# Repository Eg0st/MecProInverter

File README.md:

# Goal
This project is a student project at the Munich University of Applied Sciences.
The aim is to build and operate an inverter with an output of 3.6 kW,
which is supplied with 230 volts and can operate a motor in the frequency range of 10 to 500 Hz.
The ESP32-S3 and the SimpleFoc Bilbiotek were used for this.

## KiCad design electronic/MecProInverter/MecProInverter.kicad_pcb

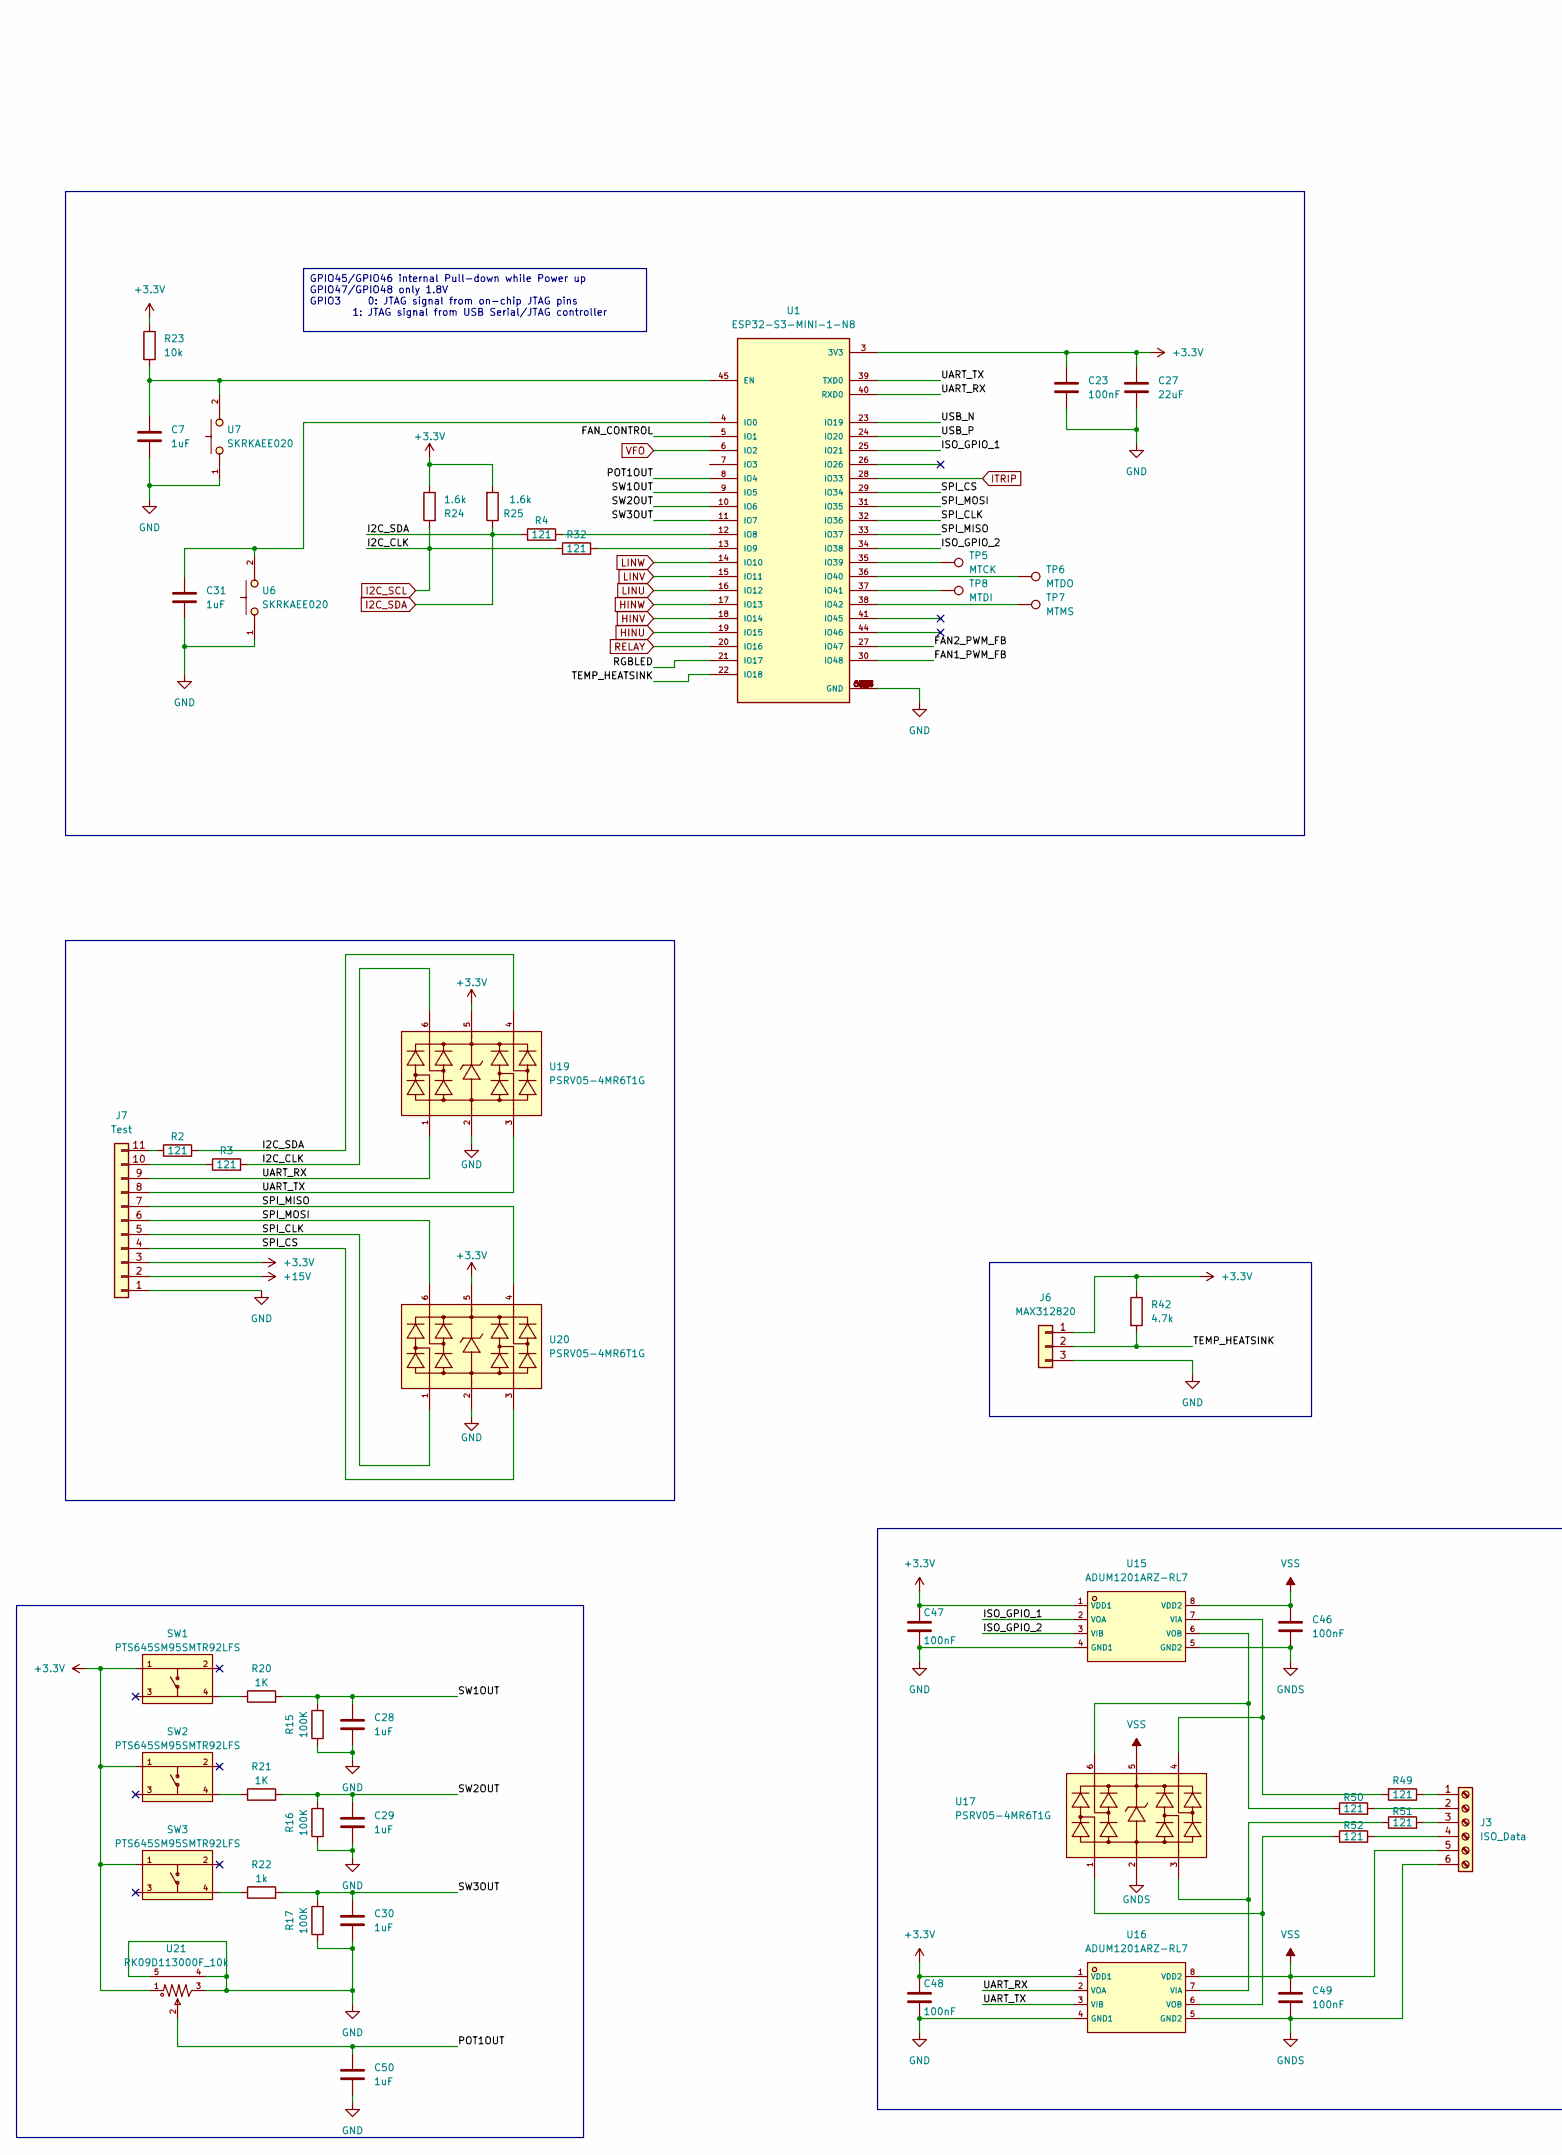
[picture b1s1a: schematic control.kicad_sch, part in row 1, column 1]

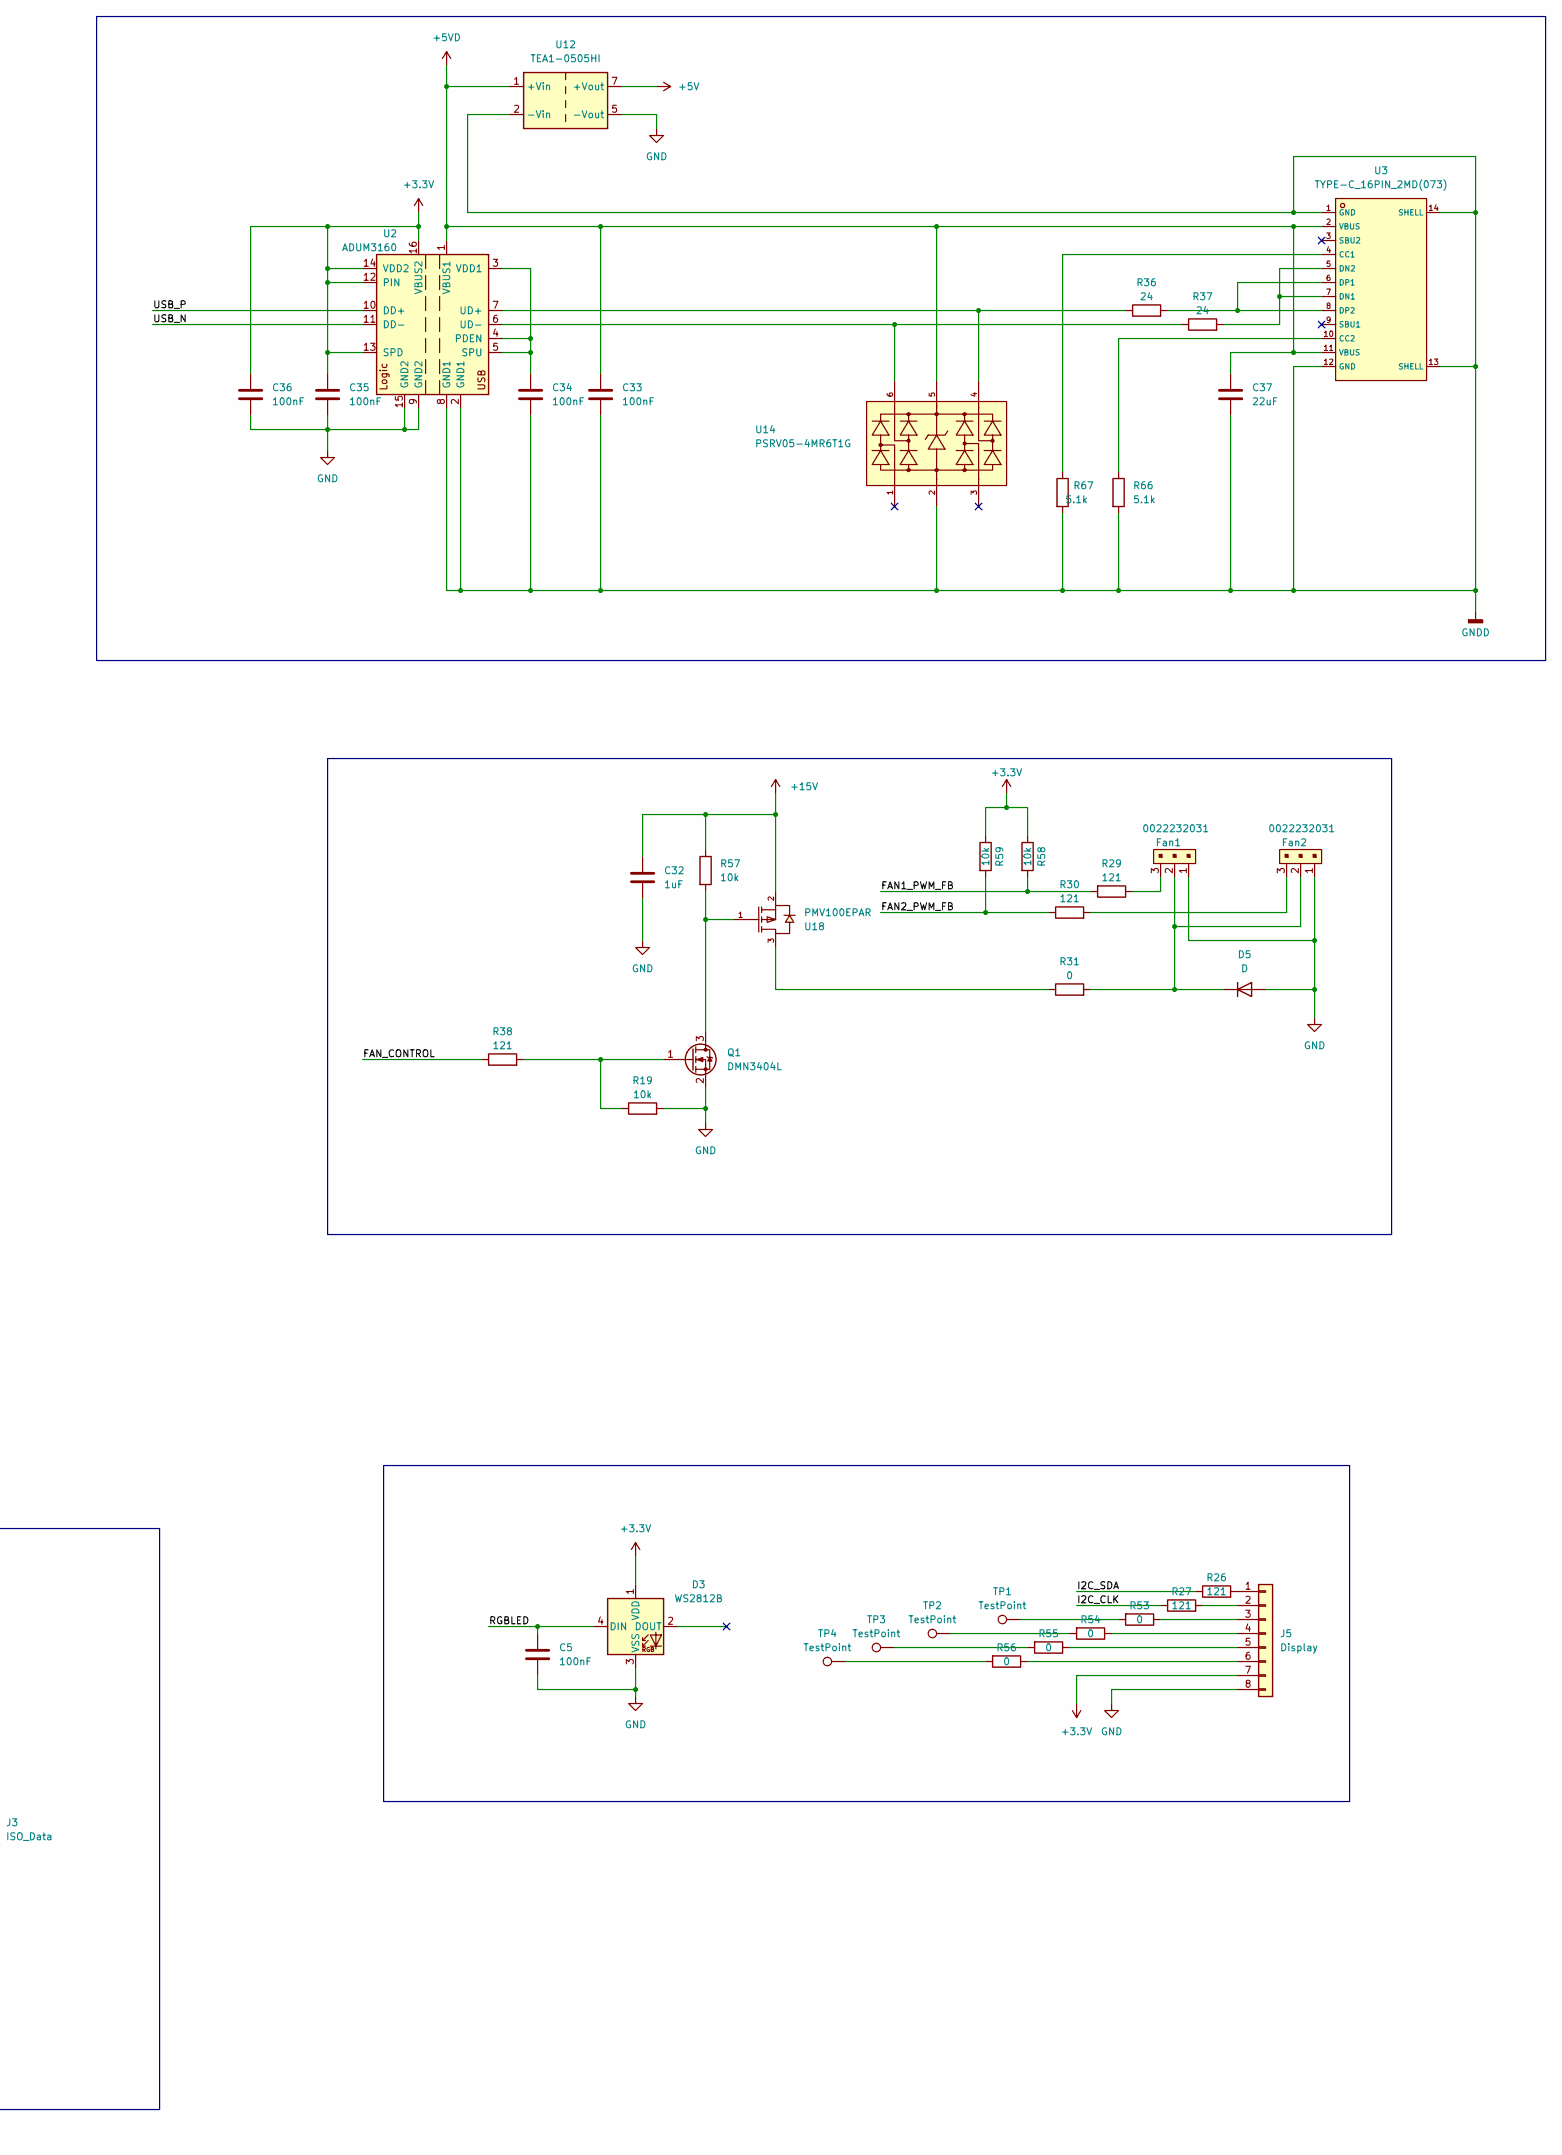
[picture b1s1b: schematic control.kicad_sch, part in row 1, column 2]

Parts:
C5, C23, C33, C34, C35, C36, C46, C47, C48, C49: 100nF; C_0603_1608Metric
C7, C28, C29, C30, C31, C32, C50: 1uF; C_0603_1608Metric
C27, C37: 22uF; C_0603_1608Metric
D3: WS2812B; LED_WS2812B_PLCC4_5.0x5.0mm_P3.2mm
D5: D; D_SOD-123
Fan1, Fan2: 0022232031; CONN-TH_3P-P2.54_22-23-2031; MPN 0022232031; Digi-Key_PN WM4201-ND
J3: ISO_Data; TerminalBlock_Phoenix_MPT-0,5-6-2.54_1x06_P2.54mm_Horizontal
J5: Display; Adafruit_938
J6: MAX312820; PinHeader_1x03_P2.54mm_Vertical
J7: Test; PinHeader_1x11_P2.54mm_Vertical
Q1: DMN3404L; SOT-23
R2, R3, R4, R26, R27, R29, R30, R32, R38, R49, R50, R51, R52: 121; R_0603_1608Metric
R15, R16, R17: 100K; R_0603_1608Metric
R19, R23, R57, R58, R59: 10k; R_0603_1608Metric
R20, R21: 1K; R_0603_1608Metric
R22: 1k; R_0603_1608Metric
R24, R25: 1.6k; R_0603_1608Metric
R31: 0; R_1206_3216Metric
R36, R37: 24; R_0603_1608Metric
R42: 4.7k; R_0603_1608Metric
R53, R54, R55, R56: 0; R_0603_1608Metric
R66, R67: 5.1k; R_0603_1608Metric
SW1, SW2, SW3: PTS645SM95SMTR92LFS; KEY-SMD_4P-L6.1-W6.1-P4.50-LS9.0; LCSC C221884
TP1, TP2, TP3, TP4: TestPoint; TestPoint_Pad_D1.5mm
TP5: MTCK; TestPoint_Pad_D1.5mm
TP6: MTDO; TestPoint_Pad_D1.5mm
TP7: MTMS; TestPoint_Pad_D1.5mm
TP8: MTDI; TestPoint_Pad_D1.5mm
U1: ESP32-S3-MINI-1-N8; BULETM-SMD_ESP32-S3-MINI-1-N8; PARTREV v0.6
U2: ADUM3160; SOIC-16W_7.5x10.3mm_P1.27mm
U3: TYPE-C_16PIN_2MD(073); USB-C-SMD_TYPE-C-6PIN-2MD-073; LCSC C2765186
U6, U7: SKRKAEE020; SW-SMD_L3.9-W3.0-P4.45; LCSC C115357
U12: TEA1-0505HI; Converter_DCDC_TRACO_TEA1HI-xxxx_THT
U14, U17, U19, U20: PSRV05-4MR6T1G; SOT-23-6_L2.9-W1.6-P0.95-LS2.8-BL; LCSC C2936987
U15, U16: ADUM1201ARZ-RL7; SOIC-8_L4.9-W3.9-P1.27-LS6.0-BL; LCSC C9669
U18: PMV100EPAR; SOT-23-3_L2.9-W1.3-P1.90-LS2.3-BR; LCSC C3290636
U21: RK09D113000F_10k; RES-ADJ-TH_RK09D1130C4G; LCSC C470317

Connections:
+3.3V: C23.1, C27.1, C35.1, C36.1, C47.1, C48.1, D3.1 (VDD), J5.7, J6.1, J7.3, R23.1, R24.1, R25.2, R42.1, R58.1, R59.1, SW1.1, SW2.1, SW3.1, U1.3 (3V3), U2.12 (PIN), U2.13 (SPD), U2.14 (VDD2), U2.16 (VBUS2), U15.1 (VDD1), U16.1 (VDD1), U19.5, U20.5, U21.1; also elsewhere on the board
+5V: U12.7 (+Vout); also elsewhere on the board
+5VD: C33.1, C37.1, U2.1 (VBUS1), U3.2 (VBUS), U3.11 (VBUS), U12.1 (+Vin), U14.5
+15V: C32.1, J7.2, R57.1, U18.2 (S); also elsewhere on the board
/Control/FAN1_PWM_FB: R29.2, R58.2, U1.30 (IO48)
/Control/FAN2_PWM_FB: R30.1, R59.2, U1.27 (IO47)
/Control/FAN_CONTROL: R38.1, U1.5 (IO1)
/Control/ISO_GPIO_1: U1.25 (IO21), U15.2 (VOA)
/Control/ISO_GPIO_2: U1.34 (IO38), U15.3 (VIB)
/Control/POT1OUT: C50.1, U1.8 (IO4), U21.2
/Control/RGBLED: C5.1, D3.4 (DIN), U1.21 (IO17)
/Control/SPI_CLK: J7.5, U1.32 (IO36), U20.1
/Control/SPI_CS: J7.4, U1.29 (IO34), U20.3
/Control/SPI_MISO: J7.7, U1.33 (IO37), U20.4
/Control/SPI_MOSI: J7.6, U1.31 (IO35), U20.6
/Control/SW1OUT: C28.1, R15.2, R20.2, U1.9 (IO5)
/Control/SW2OUT: C29.1, R16.2, R21.2, U1.10 (IO6)
/Control/SW3OUT: C30.1, R17.2, R22.2, U1.11 (IO7)
/Control/TEMP_HEATSINK: J6.2, R42.2, U1.22 (IO18)
/Control/UART_RX: J7.9, U1.40 (RXD0), U16.2 (VOA), U19.1
/Control/UART_TX: J7.8, U1.39 (TXD0), U16.3 (VIB), U19.3
/Control/USB_N: U1.23 (IO19), U2.11 (DD-)
/Control/USB_P: U1.24 (IO20), U2.10 (DD+)
GND: C5.2, C7.2, C23.2, C27.2, C28.2, C29.2, C30.2, C31.2, C32.2, C35.2, C36.2, C47.2, C48.2, C50.2, D3.3 (VSS), D5.2 (A), Fan1.1, Fan2.1, J5.8, J6.3, J7.1, Q1.2 (S), R15.1, R16.1, R17.1, R19.2, U1.1 (GND), U1.2 (GND), U1.42 (GND), U1.43 (GND), U1.46 (GND), U1.47 (GND), U1.48 (GND), U1.49 (GND), U1.50 (GND), U1.51 (GND), U1.52 (GND), U1.53 (GND), U1.54 (GND), U1.55 (GND), U1.56 (GND), U1.57 (GND), U1.58 (GND), U1.59 (GND), U1.60 (GND), U1.61 (GND), U1.61_1 (GND), U1.61_2 (GND), U1.61_3 (GND), U1.61_4 (GND), U1.61_5 (GND), U1.61_6 (GND), U1.61_7 (GND), U1.61_8 (GND), U1.62 (GND), U1.63 (GND), U1.64 (GND), U1.65 (GND), U2.9 (GND2), U2.15 (GND2), U6.1, U7.1, U12.5 (-Vout), U15.4 (GND1), U16.4 (GND1), U19.2, U20.2, U21.3, U21.4, U21.5; also elsewhere on the board
GNDD: C33.2, C34.2, C37.2, R66.2, R67.2, U2.2 (GND1), U2.8 (GND1), U3.1 (GND), U3.12 (GND), U3.13 (SHELL), U3.14 (SHELL), U12.2 (-Vin), U14.2
GNDS: C46.2, C49.2, J3.6, U15.5 (GND2), U16.5 (GND2), U17.2
HINU: U1.19 (IO15); also elsewhere on the board
HINV: U1.18 (IO14); also elsewhere on the board
HINW: U1.17 (IO13); also elsewhere on the board
I2C_SCL: R3.2, R24.2, R27.1, R32.1, U19.6; also elsewhere on the board
I2C_SDA: R2.2, R4.1, R25.1, R26.1, U19.4; also elsewhere on the board
ITRIP: U1.28 (IO33); also elsewhere on the board
LINU: U1.16 (IO12); also elsewhere on the board
LINV: U1.15 (IO11); also elsewhere on the board
LINW: U1.14 (IO10); also elsewhere on the board
unnamed: D5.1 (K), Fan1.2, Fan2.2, R31.2
unnamed: Fan1.3, R29.1
unnamed: Fan2.3, R30.2
unnamed: J3.1, R49.1
unnamed: J3.2, R50.2
unnamed: J3.3, R51.2
unnamed: J3.4, R52.2
unnamed: J5.1, R26.2
unnamed: J5.2, R27.2
unnamed: J5.3, R53.1
unnamed: J5.4, R54.1
unnamed: J5.5, R55.1
unnamed: J5.6, R56.1
unnamed: J7.10, R3.1
unnamed: J7.11, R2.1
unnamed: R20.1, SW1.4
unnamed: R21.1, SW2.4
unnamed: R22.1, SW3.4
unnamed: R53.2, TP1.1
unnamed: R54.2, TP2.1
unnamed: R55.2, TP3.1
unnamed: R56.2, TP4.1
unnamed: C7.1, R23.2, U1.45 (EN), U7.2
unnamed: C31.1, U1.4 (IO0), U6.2
unnamed: R4.2, U1.12 (IO8)
unnamed: R32.2, U1.13 (IO9)
unnamed: TP5.1, U1.35 (IO39)
unnamed: TP6.1, U1.36 (IO40)
unnamed: TP8.1, U1.37 (IO41)
unnamed: TP7.1, U1.38 (IO42)
unnamed: C34.1, U2.3 (VDD1), U2.4 (PDEN), U2.5 (SPU)
unnamed: R36.1, U2.7 (UD+), U14.4
unnamed: R37.1, U2.6 (UD-), U14.6
unnamed: R67.1, U3.4 (CC1)
unnamed: R66.1, U3.10 (CC2)
unnamed: R37.2, U3.5 (DN2), U3.7 (DN1)
unnamed: R36.2, U3.6 (DP1), U3.8 (DP2)
unnamed: R49.2, U15.7 (VIA), U17.4
unnamed: R50.1, U15.6 (VOB), U17.6
unnamed: R51.1, U16.7 (VIA), U17.3
unnamed: R52.1, U16.6 (VOB), U17.1
unnamed: R31.1, U18.3 (D)
RELAY: U1.20 (IO16); also elsewhere on the board
VFO: U1.6 (IO2); also elsewhere on the board
VSS: C46.1, C49.1, J3.5, U15.8 (VDD2), U16.8 (VDD2), U17.5

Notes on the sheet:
GPIO45/GPIO46 internal Pull-down while Power up GPIO47/GPIO48 only 1.8V GPIO3 0: JTAG signal from on-chip JTAG pins 1: JTAG signal from USB Serial/JTAG controller

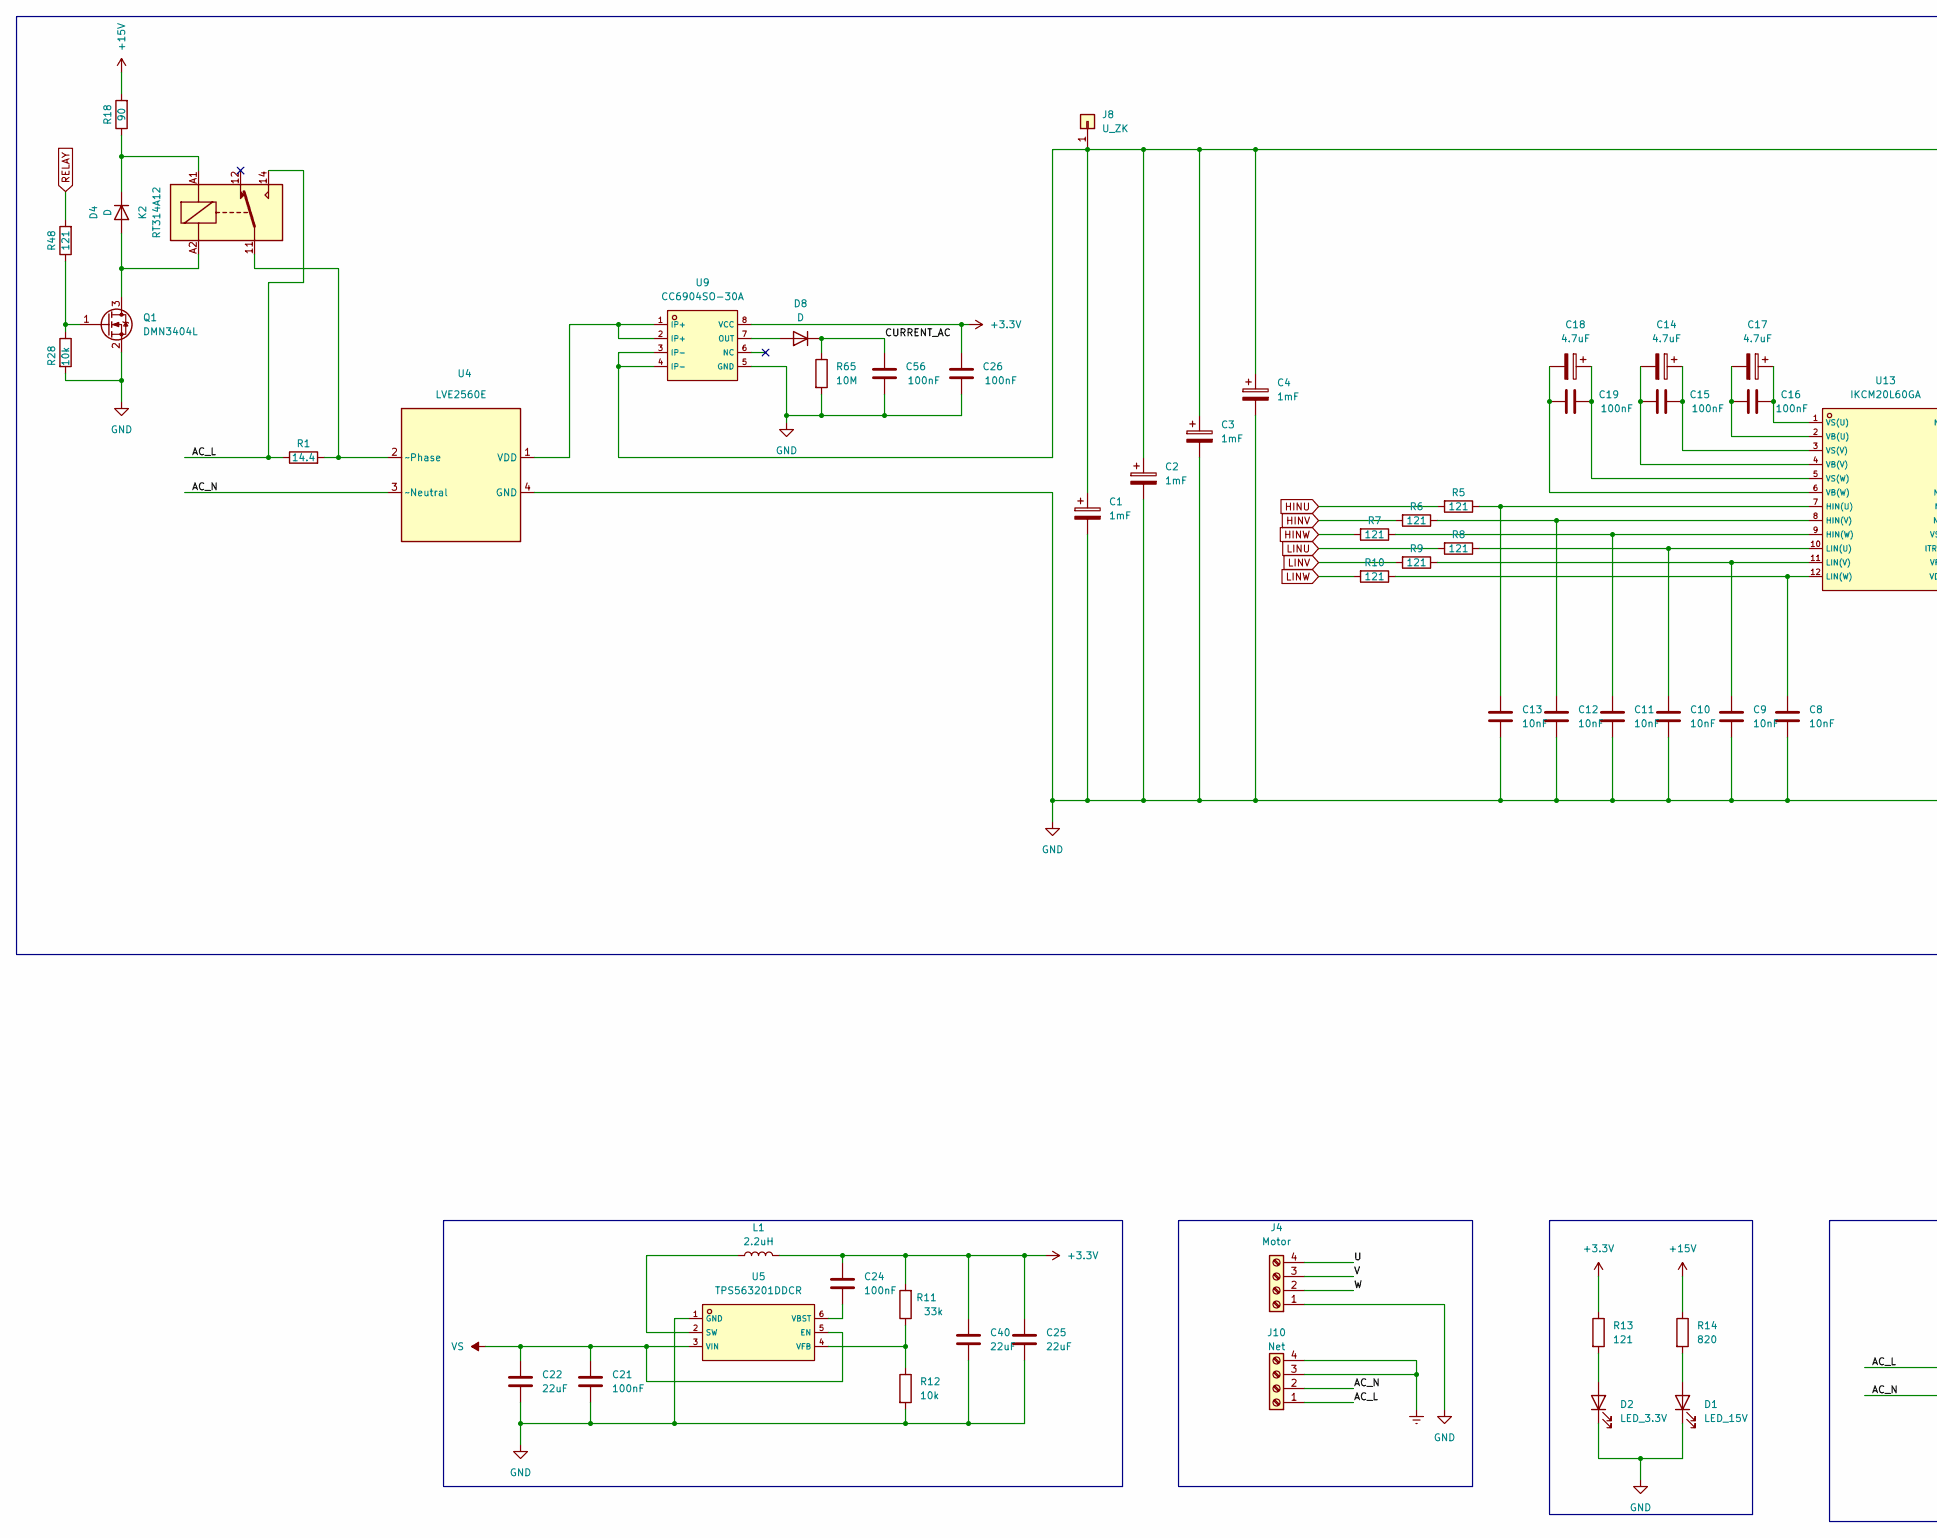
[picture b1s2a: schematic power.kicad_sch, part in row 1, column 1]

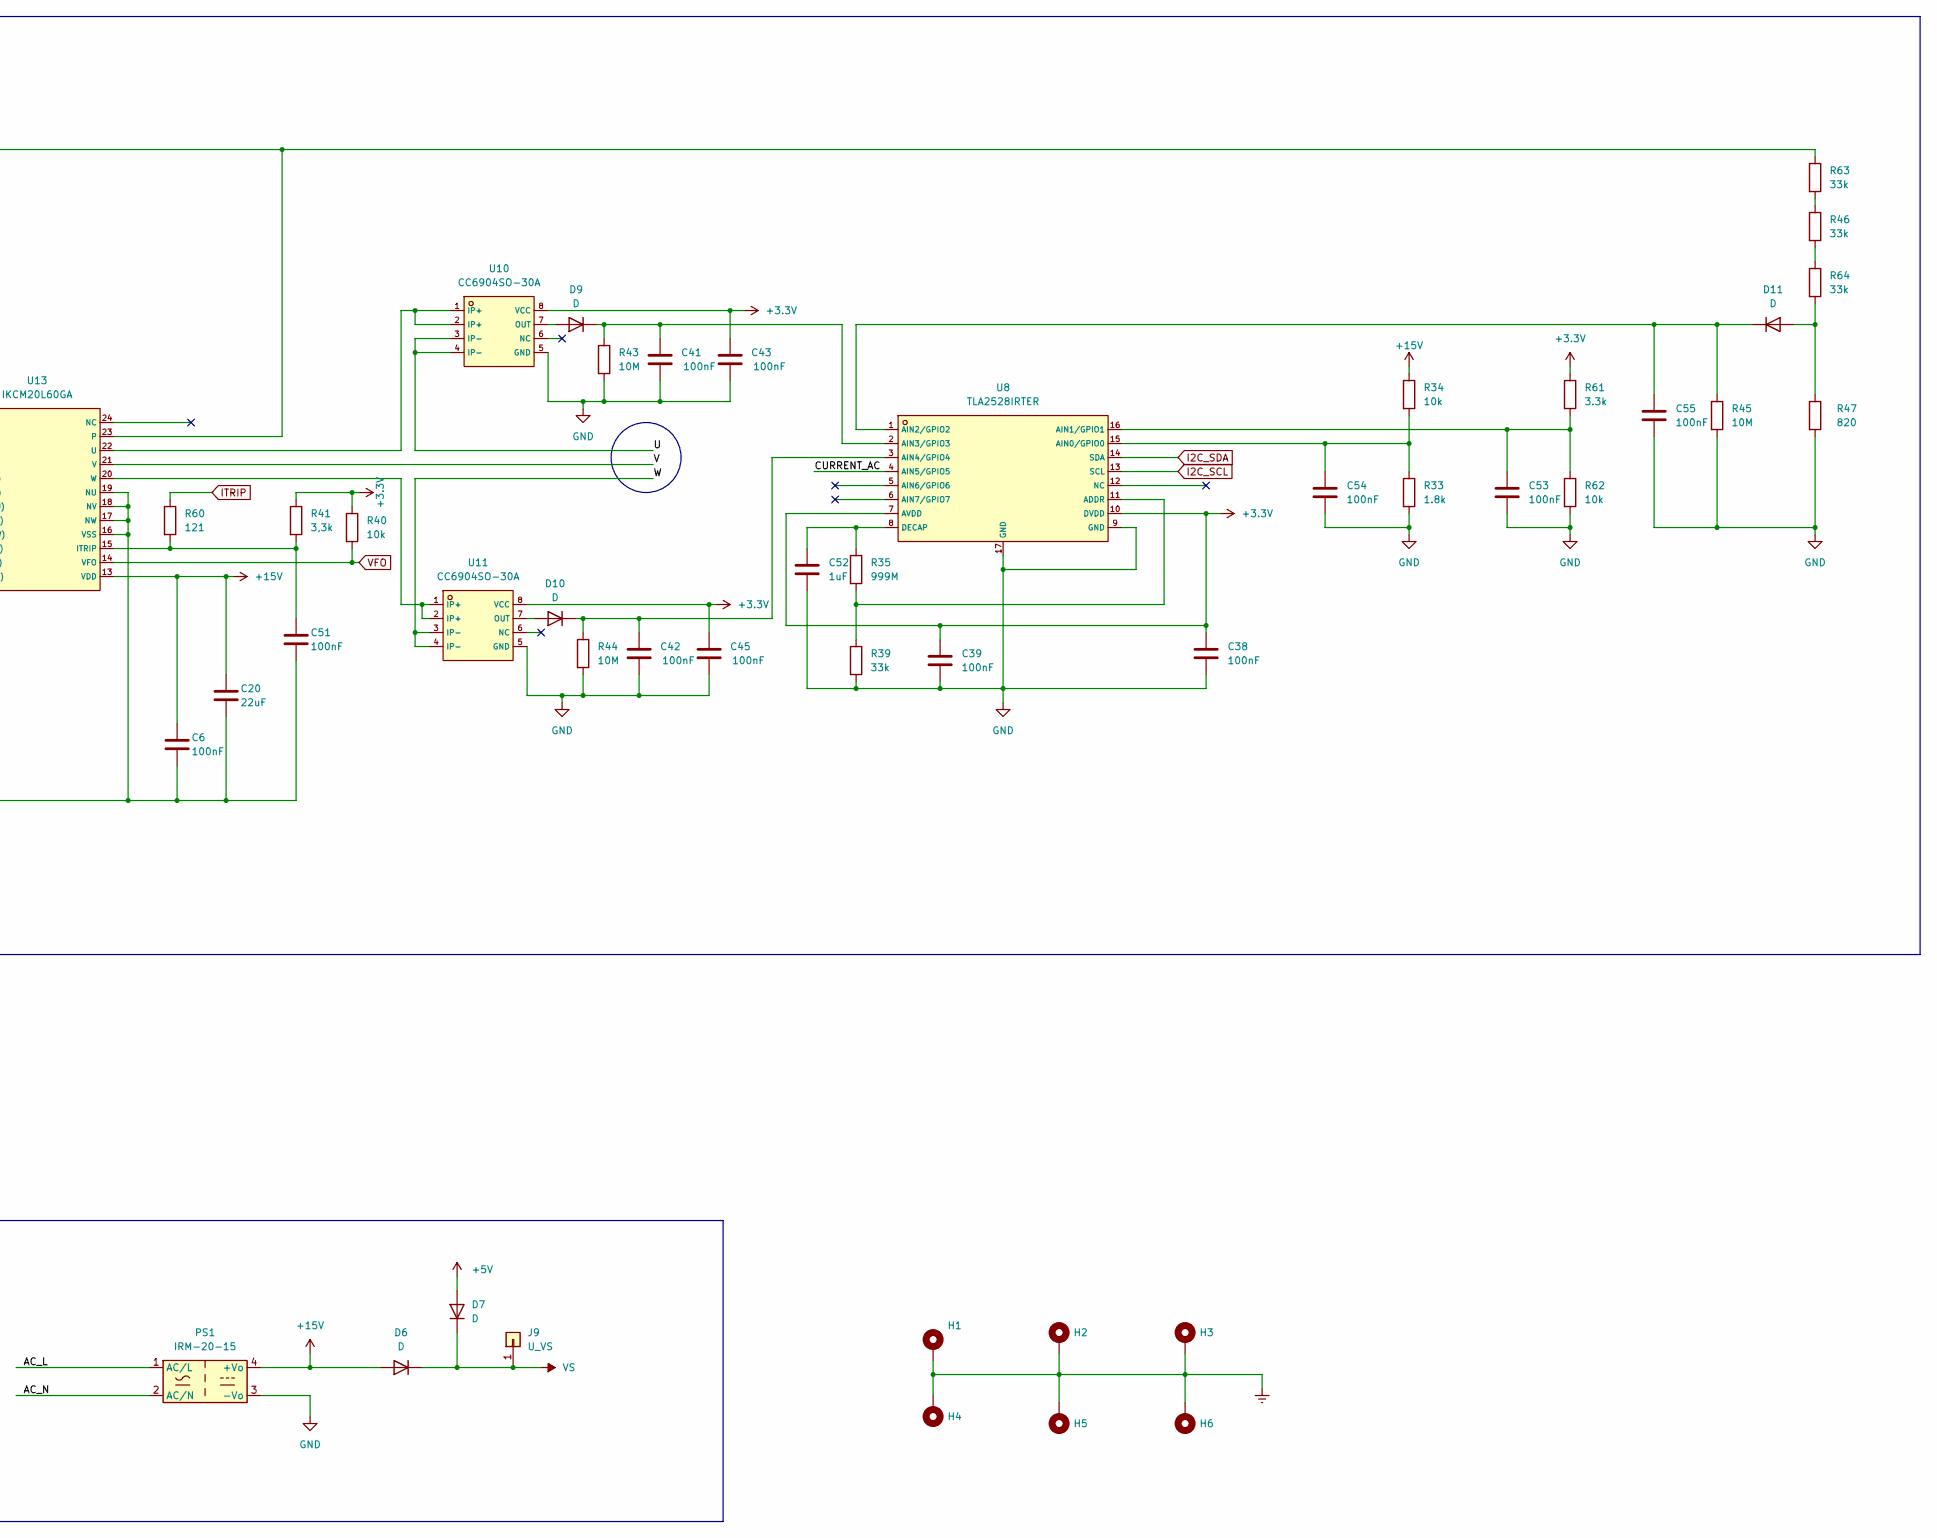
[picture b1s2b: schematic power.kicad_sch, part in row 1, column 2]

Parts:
C1, C2, C3, C4: 1mF; ESMQ351VSN102MA50S
C6, C15, C16, C19, C21, C24, C26, C38, C39, C41, C42, C43, C45, C51, C53, C54, C55, C56: 100nF; C_0603_1608Metric
C8, C9, C10, C11, C12, C13: 10nF; C_0603_1608Metric
C14, C17, C18: 4.7uF; C_0603_1608Metric
C20, C22, C25, C40: 22uF; C_0603_1608Metric
C52: 1uF; C_0603_1608Metric
D1: LED_15V; LED_0603_1608Metric
D2: LED_3.3V; LED_0603_1608Metric
D4, D6, D7: D; D_SOD-123
D8, D9, D10, D11: D; D_0603_1608Metric
H1, H2, H3, H4, H5, H6: MountingHole_3.2mm_M3_DIN965_Pad_TopBottom
J4: Motor; TerminalBlock_Phoenix_PT-1,5-4-5.0-H_1x04_P5.00mm_Horizontal
J8: U_ZK; PinHeader_1x01_P2.54mm_Vertical
J9: U_VS; PinHeader_1x01_P2.54mm_Vertical
J10: Net; TerminalBlock_Phoenix_PT-1,5-4-5.0-H_1x04_P5.00mm_Horizontal
K2: RT314A12; Relay_SPDT_Schrack-RT1-16A-FormC_RM5mm
L1: 2.2uH; L_Bourns_SRP7028A_7.3x6.6mm
PS1: IRM-20-15; Converter_ACDC_MeanWell_IRM-20-xx_THT
Q1: DMN3404L; SOT-23
R1: 14.4; PWR220T-20
R5, R6, R7, R8, R9, R10, R13, R48, R60: 121; R_0603_1608Metric
R11, R39: 33k; R_0603_1608Metric
R12, R28, R34, R40, R62: 10k; R_0603_1608Metric
R14, R47: 820; R_0603_1608Metric
R18: 90; R_1206_3216Metric
R33: 1.8k; R_0603_1608Metric
R35: 999M; R_0603_1608Metric
R41: 3,3k; R_0603_1608Metric
R43, R44, R45, R65: 10M; R_0603_1608Metric
R46, R63, R64: 33k; R_1206_3216Metric
R61: 3.3k; R_0603_1608Metric
U4: LVE2560E
U5: TPS563201DDCR; SOT-23-6_L2.9-W1.6-P0.95-LS2.8-BL; LCSC C116592
U8: TLA2528IRTER; WQFN-16_L3.0-W3.0-P0.50-TL-EP1.7; LCSC C2866175
U9, U10, U11: CC6904SO-30A; SOP-8_L4.9-W3.9-P1.27-LS6.0-BL; LCSC C521203
U13: IKCM20L60GA; DIP-24_L36.0-W21.0-P1.60-LS28.6-TL; LCSC C536161

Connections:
+3.3V: C24.1, C25.1, C26.2, C38.2, C39.1, C40.1, C43.2, C45.2, L1.2, R11.2, R13.1, R40.1, R41.1, R61.1, U8.7 (AVDD), U8.10 (DVDD), U9.8 (VCC), U10.8 (VCC), U11.8 (VCC); also elsewhere on the board
+5V: D7.2 (A); also elsewhere on the board
+15V: C6.1, C20.1, D6.2 (A), PS1.4 (+Vo), R14.1, R18.2, R34.1, U13.13 (VDD); also elsewhere on the board
/Power/AC_L: J10.1, K2.14, PS1.1 (AC/L), R1.1
/Power/AC_N: J10.2, PS1.2 (AC/N), U4.3 (~Neutral)
/Power/CURRENT_AC: C56.2, D8.1 (K), R65.1, U8.4 (AIN5/GPIO5)
/Power/U: J4.4, U10.3 (IP-), U10.4 (IP-)
/Power/V: J4.3, U13.21 (V)
/Power/W: J4.2, U11.3 (IP-), U11.4 (IP-)
Earth: H1.1, H2.1, H3.1, H4.1, H5.1, H6.1, J10.3, J10.4
GND: C1.2, C2.2, C3.2, C4.2, C6.2, C8.2, C9.2, C10.2, C11.2, C12.2, C13.2, C20.2, C21.2, C22.2, C25.2, C26.1, C38.1, C39.2, C40.2, C41.1, C42.1, C43.1, C45.1, C51.2, C52.2, C53.2, C54.2, C55.2, C56.1, J4.1, PS1.3 (-Vo), Q1.2 (S), R12.2, R28.2, R33.2, R39.2, R43.2, R44.2, R45.2, R47.2, R62.2, R65.2, U4.4 (GND), U5.1 (GND), U8.9 (GND), U8.17 (GND), U9.5 (GND), U10.5 (GND), U11.5 (GND), U13.16 (VSS), U13.17 (NW), U13.18 (NV), U13.19 (NU); also elsewhere on the board
HINU: R5.2; also elsewhere on the board
HINV: R6.2; also elsewhere on the board
HINW: R7.2; also elsewhere on the board
I2C_SCL: U8.13 (SCL); also elsewhere on the board
I2C_SDA: U8.14 (SDA); also elsewhere on the board
ITRIP: R60.1; also elsewhere on the board
LINU: R8.2; also elsewhere on the board
LINV: R9.2; also elsewhere on the board
LINW: R10.2; also elsewhere on the board
unnamed 42: R13.2; also elsewhere on the board
unnamed: D4.1 (K), K2.A1, R18.1
unnamed: D8.2 (A), U9.7 (OUT)
unnamed: D9.2 (A), U10.7 (OUT)
unnamed: C41.2, D9.1 (K), R43.1, U8.2 (AIN3/GPIO3)
unnamed: D10.2 (A), U11.7 (OUT)
unnamed: C42.2, D10.1 (K), R44.1, U8.3 (AIN4/GPIO4)
unnamed: D11.2 (A), R47.1, R64.2
unnamed: C55.1, D11.1 (K), R45.1, U8.1 (AIN2/GPIO2)
unnamed 52: R14.2; also elsewhere on the board
unnamed: C1.1, C2.1, C3.1, C4.1, J8.1, R63.1, U9.3 (IP-), U9.4 (IP-), U13.23
unnamed: R46.1, R63.2
unnamed: R46.2, R64.1
unnamed: U4.1 (VDD), U9.1 (IP+), U9.2 (IP+)
unnamed: K2.11, R1.2, U4.2 (~Phase)
unnamed: L1.1, U5.2 (SW)
unnamed: C24.2, U5.6 (VBST)
unnamed: R11.1, R12.1, U5.4 (VFB)
unnamed: R35.2, R39.1, U8.11 (ADDR)
unnamed: C54.1, R33.1, R34.2, U8.15 (AIN0/GPIO0)
unnamed: C53.1, R61.2, R62.1, U8.16 (AIN1/GPIO1)
unnamed: C52.1, R35.1, U8.8 (DECAP)
unnamed: C13.1, R5.1, U13.7 (HIN(U))
unnamed: C12.1, R6.1, U13.8 (HIN(V))
unnamed: C11.1, R7.1, U13.9 (HIN(W))
unnamed: C51.1, R41.2, R60.2, U13.15 (ITRIP)
unnamed: C10.1, R8.1, U13.10 (LIN(U))
unnamed: C9.1, R9.1, U13.11 (LIN(V))
unnamed: C8.1, R10.1, U13.12 (LIN(W))
unnamed: U10.1 (IP+), U10.2 (IP+), U13.22 (U)
unnamed: C16.1, C17.2, U13.2 (VB(U))
unnamed: C14.2, C15.1, U13.4 (VB(V))
unnamed: C18.2, C19.1, U13.6 (VB(W))
unnamed: C16.2, C17.1, U13.1 (VS(U))
unnamed: C14.1, C15.2, U13.3 (VS(V))
unnamed: C18.1, C19.2, U13.5 (VS(W))
unnamed: U11.1 (IP+), U11.2 (IP+), U13.20 (W)
RELAY: R48.2; also elsewhere on the board
VFO: R40.2, U13.14 (VFO); also elsewhere on the board
VS: C21.1, C22.1, D6.1 (K), D7.1 (K), J9.1, U5.3 (VIN), U5.5 (EN)

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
